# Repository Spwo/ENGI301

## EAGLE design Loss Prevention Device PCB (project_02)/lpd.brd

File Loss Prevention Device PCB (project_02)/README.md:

# Loss Prevention Device PCB (Project_02)

This folder contains the neccesary files for creating a printed circuit board for the loss prevention device

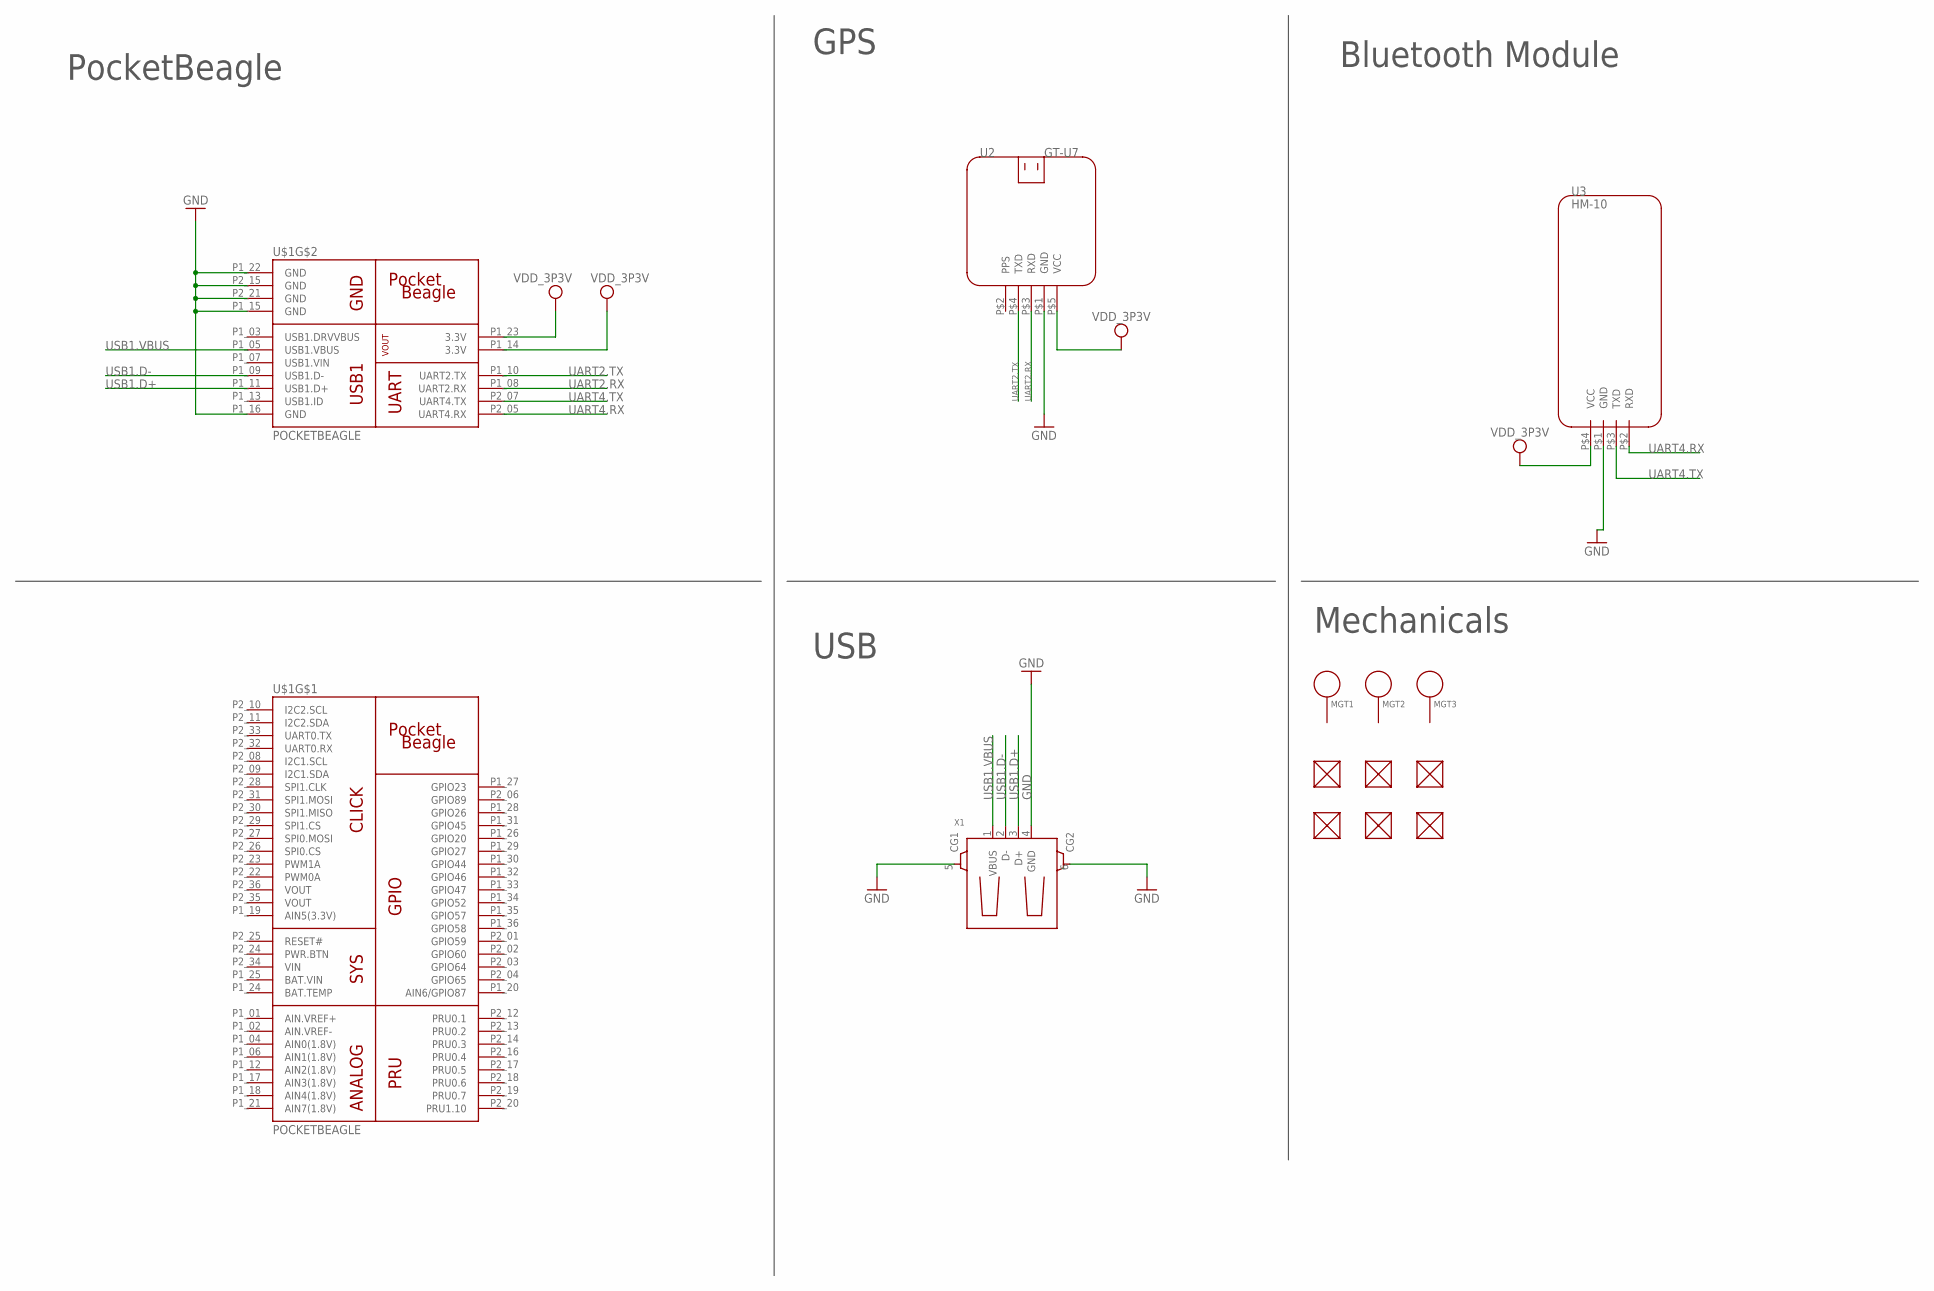
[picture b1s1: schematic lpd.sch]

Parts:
FUD1, FUD2, FUD3, FUD4, FUD5, FUD6: FIDUCIAL; FIDUCIAL_40MIL
MGT1, MGT2, MGT3: MOUNTING_HOLE
U2: GT-U7; GPS
U3: HM-10; BT
U$1: POCKETBEAGLE
X1: GHI2_USB_HOST_W/CHASSIS_GND; GHI2_USB_HOST_HORIZONTAL_W/CHASSIS_GND

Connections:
BAT.VIN: U$1.P1_25 (BAT.VIN)
GND: U2.P$1 (GND), U3.P$1 (GND), U$1.P1_15 (GND), U$1.P1_16 (GND), U$1.P1_22 (GND), U$1.P2_15 (GND), U$1.P2_21 (GND), X1.4 (GND), X1.5 (CG1), X1.6 (CG2)
UART2.RX: U2.P$3 (RXD), U$1.P1_08 (UART2.RX)
UART2.TX: U2.P$4 (TXD), U$1.P1_10 (UART2.TX)
UART4.RX: U3.P$2 (RXD), U$1.P2_05 (UART4.RX)
UART4.TX: U3.P$3 (TXD), U$1.P2_07 (UART4.TX)
USB1.D+: U$1.P1_11 (USB1.D+), X1.3 (D+)
USB1.D-: U$1.P1_09 (USB1.D-), X1.2 (D-)
USB1.VBUS: U$1.P1_05 (USB1.VBUS), X1.1 (VBUS)
VDD_3P3V: U2.P$5 (VCC), U3.P$4 (VCC), U$1.P1_14 (3.3V), U$1.P1_23 (3.3V)
VIN: U$1.P2_34 (VIN)
VOUT: U$1.P2_35 (VOUT), U$1.P2_36 (VOUT)

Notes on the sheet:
PocketBeagle
GPS
USB
Bluetooth Module
Mechanicals

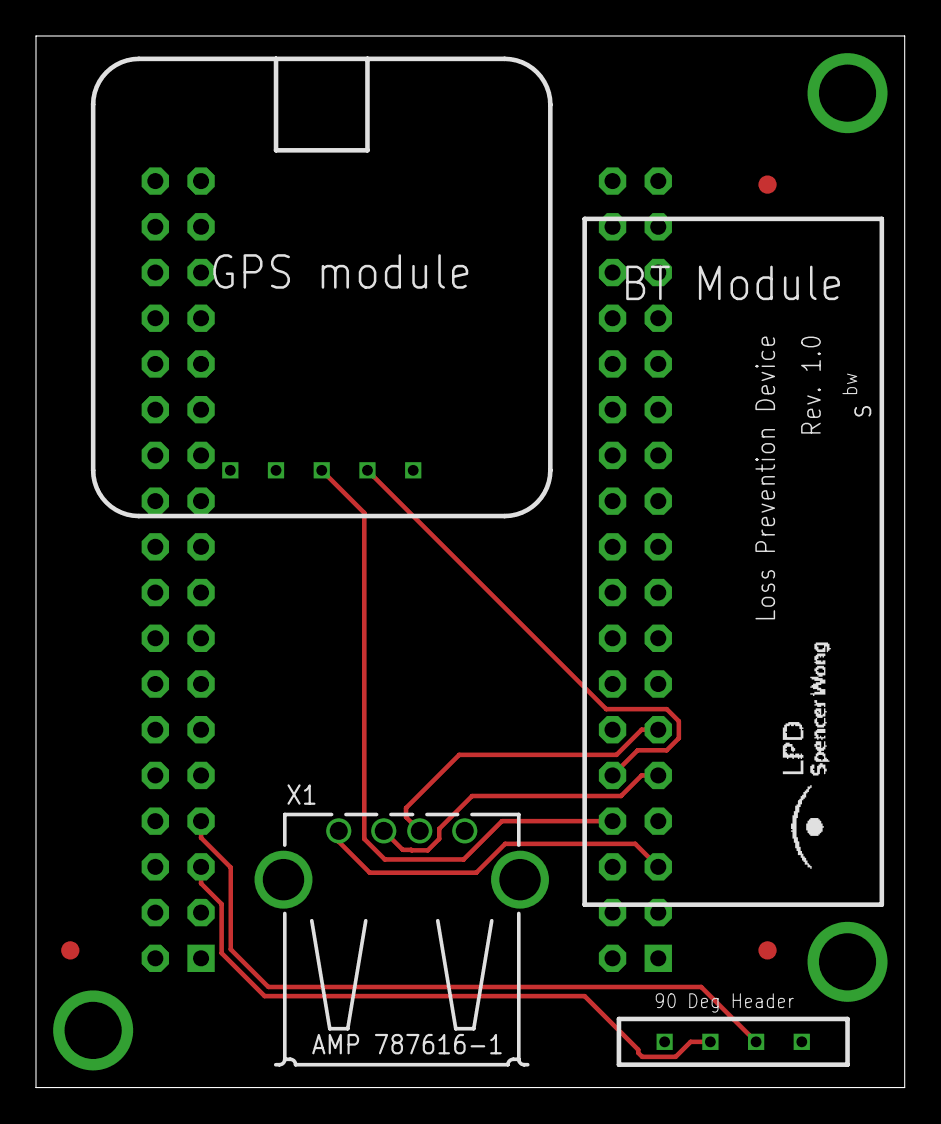
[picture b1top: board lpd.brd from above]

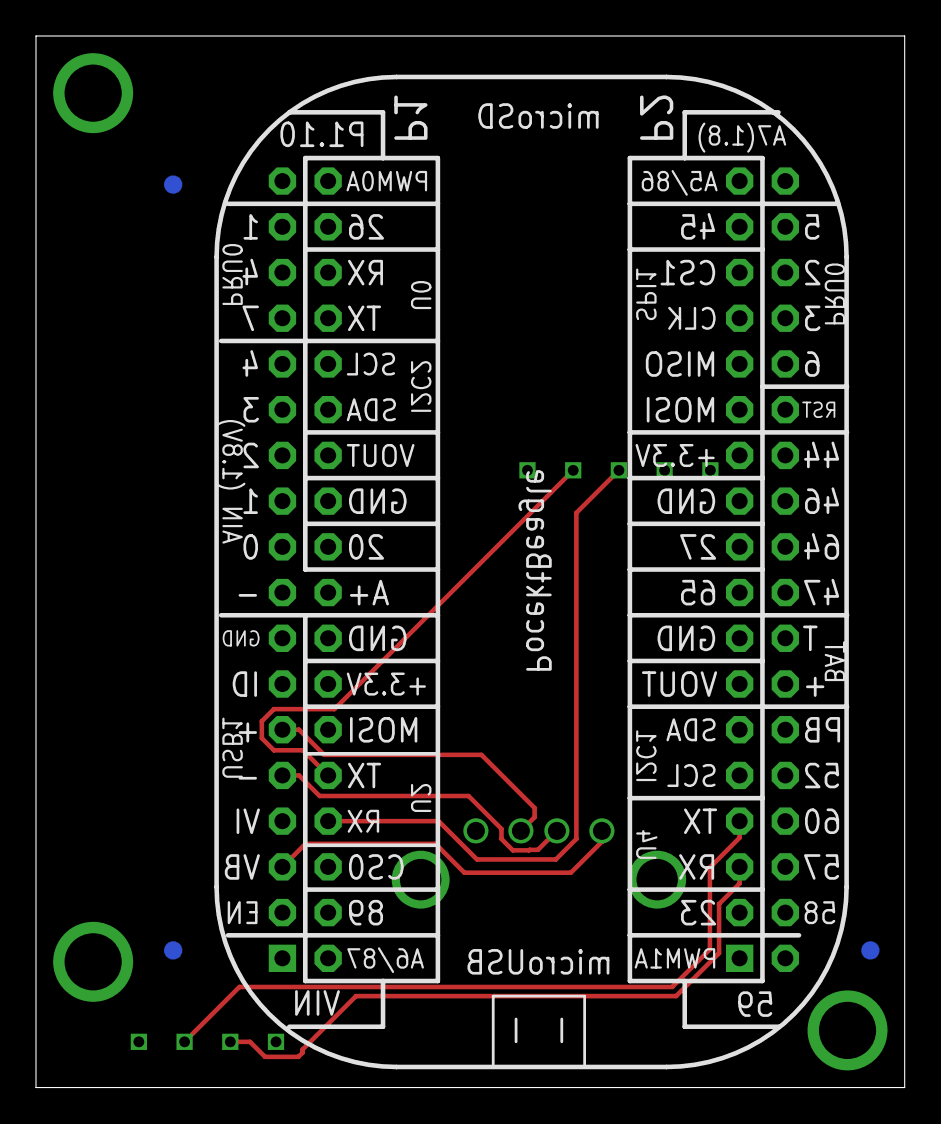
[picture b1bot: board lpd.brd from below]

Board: 4 copper layers, 48.3 x 58.4 mm, 13 parts (3 on the bottom side), 10 nets.

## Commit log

2020-09-28 Create simple_calc
2020-09-28 Fixed organization so simple_calc is now a directory
2020-09-28 Added support for 4 new operators
2020-09-28 Added backward compatibility for python 2 for the input function
2020-09-29 Minor changes to simple_calc, succesfully completed blink_USR3
2020-09-29 Update simple_calc.py
    Fixed shifts to modify floats to ints
2020-10-07 Post Project Discussion Update
2020-10-27 Added hardware verification script
2020-11-03 New GPS datasheet and python code
2020-11-04 Datasheet organization
2020-11-04 Setup WiFi module to connect to hotspot
2020-11-04 Organization
2020-11-04 Finalized hardware verification
2020-11-05 Got GPS to return value
2020-11-06 GPS Code update
    Filter out everything but the location data
2020-11-06 Updated licenses, added text messaging code
2020-11-08 Added LPD README
2020-11-09 Finalized TWILIO segment
2020-11-10 Completed GPS & text functionality
2020-11-10 OOps
2020-11-11 Fixed BT module
2020-11-11 Cleaned up folder & finalized functional code
2020-12-06 Updated MBD
2020-12-07 Creaded PCB Parts
2020-12-07 added usb
2020-12-07 Schematic'ed all parts but the usb
2020-12-07 Added USB connections
    For some reason when I imported the CGND part to my LPD library my schematic couldn't read from it anymore...
2020-12-07 Updated PocketBeagle Symbol/Footprint
2020-12-16 Split pocketbeagle symbol into 2
2020-12-16 Removed 90 degree header and updated footprints
2020-12-16 Board Placement Complete
2020-12-16 Routing
2020-12-16 Matched USB connection lengths
2020-12-16 Silkscreen cleanup
2020-12-16 Logo and Labels
2020-12-16 Document uploads
